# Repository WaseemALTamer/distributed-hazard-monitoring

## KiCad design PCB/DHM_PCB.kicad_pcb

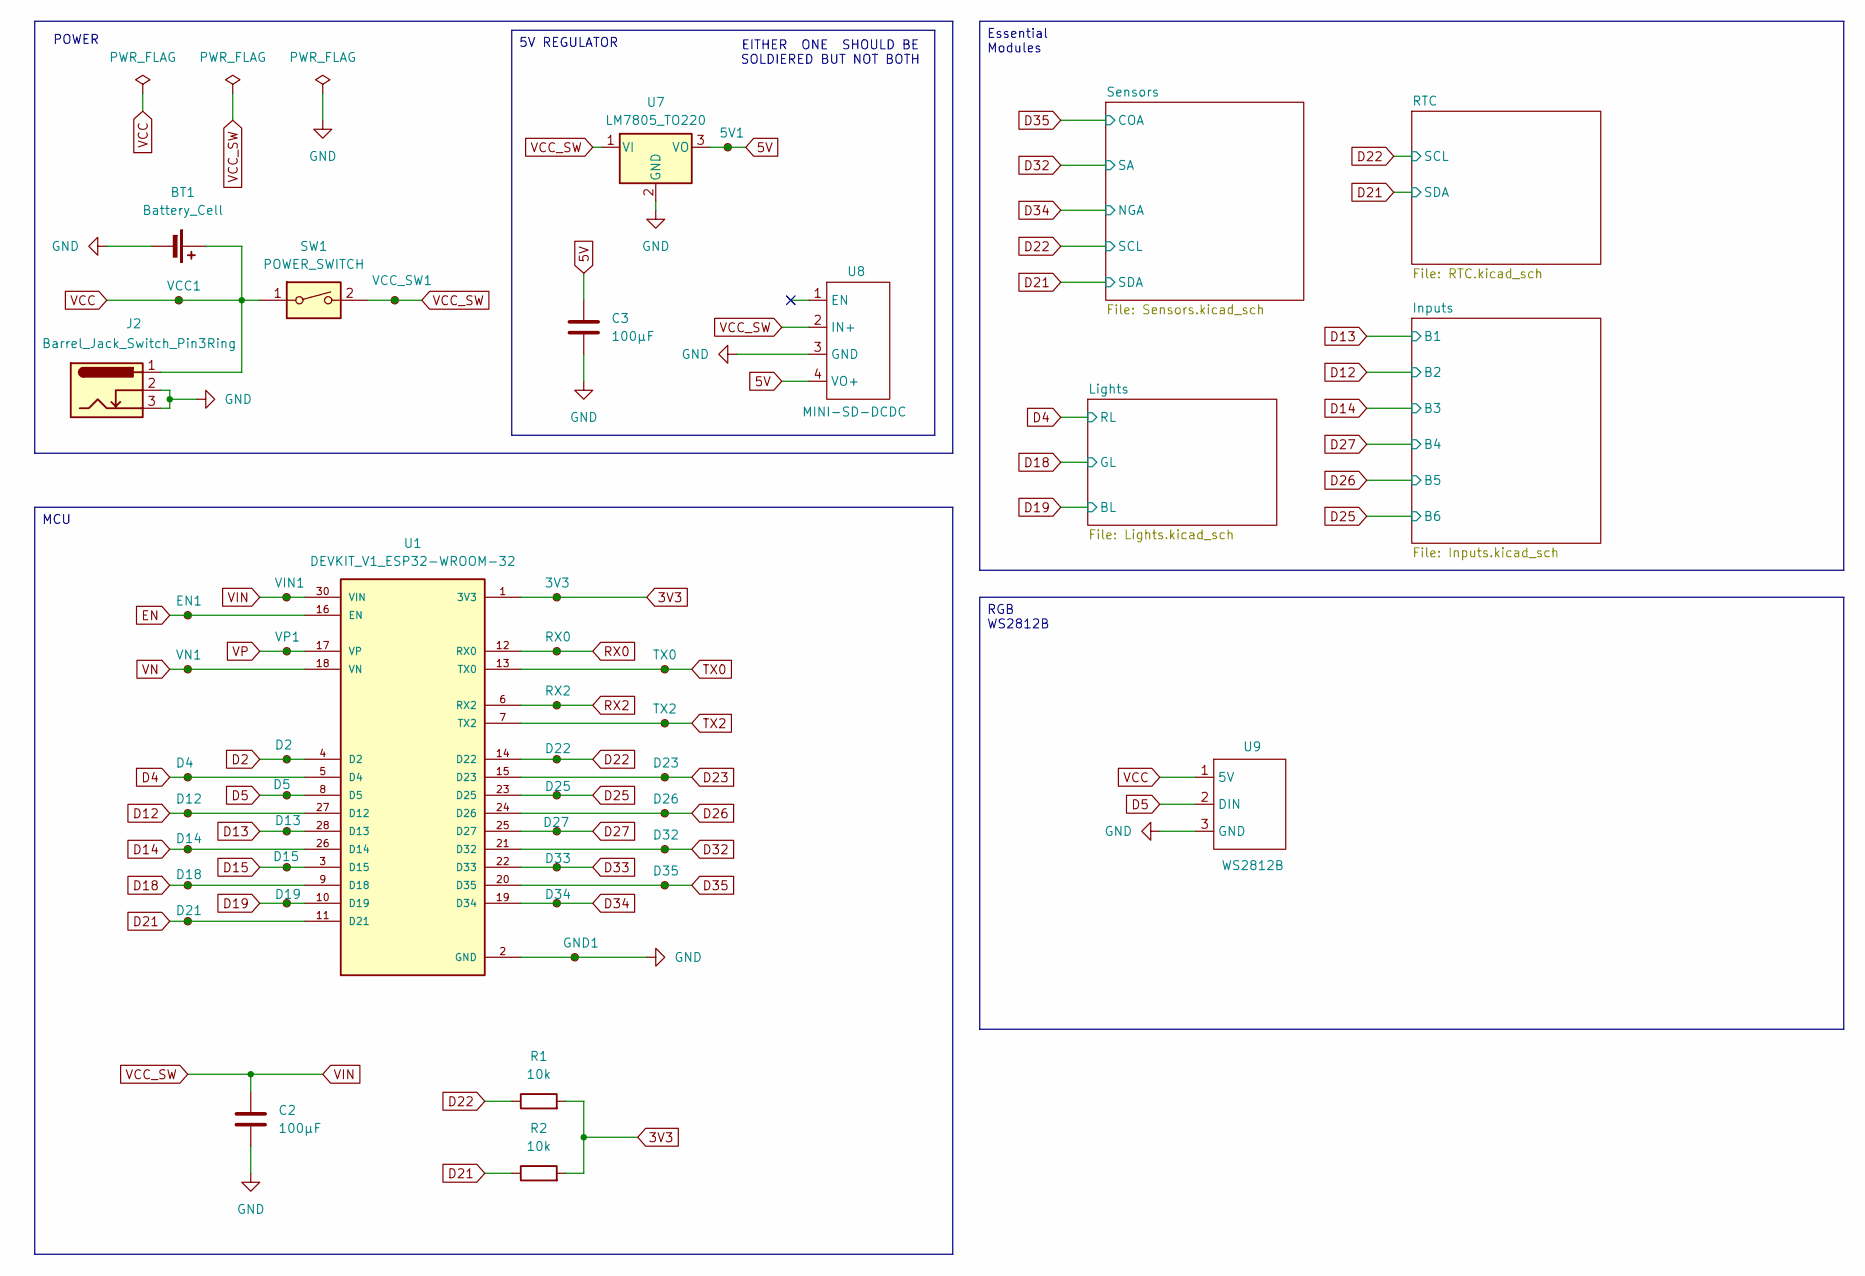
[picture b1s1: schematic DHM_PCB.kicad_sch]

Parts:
3V3, 5V1: TestPoint_Small; PinHeader_1x04_P2.54mm_Vertical_Custum_shortedpins
BT1: Battery_Cell; BatteryHolder_Eagle_12BH611-GR
C2, C3: 100µF; CP_Radial_D5.0mm_P2.00mm
D2, D4, D5, D12, D13, D14, D15, D18, D19, D21, D22, D23, D25, D26, D27, D32, D33, D34, D35: TestPoint_Small; PinHeader_1x04_P2.54mm_Vertical_Custum_shortedpins
EN1: TestPoint_Small; PinHeader_1x04_P2.54mm_Vertical_Custum_shortedpins
GND1: TestPoint_Small; PinHeader_1x04_P2.54mm_Vertical_Custum_shortedpins
J2: Barrel_Jack_Switch_Pin3Ring; BarrelJack_GCT_DCJ200-10-A_Horizontal
R1, R2: 10k; R_Axial_DIN0207_L6.3mm_D2.5mm_P10.16mm_Horizontal
RX0, RX2: TestPoint_Small; PinHeader_1x04_P2.54mm_Vertical_Custum_shortedpins
SW1: POWER_SWITCH; PinHeader_1x02_P2.54mm_Vertical
TX0, TX2: TestPoint_Small; PinHeader_1x04_P2.54mm_Vertical_Custum_shortedpins
U1: DEVKIT_V1_ESP32-WROOM-32; MODULE_DEVKIT_V1_ESP32-WROOM-32; MPN DEVKIT V1 ESP32-WROOM-32
U7: LM7805_TO220; TO-220-3_Vertical
U8: MINI-SD-DCDC; PinHeader_1x04_P2.54mm_Vertical
U9: WS2812B; TerminalBlock_Phoenix_MPT-0,5-3-2.54_1x03_P2.54mm_Horizontal
VCC1: TestPoint_Small; PinHeader_1x04_P2.54mm_Vertical_Custum_shortedpins
VCC_SW1: TestPoint_Small; PinHeader_1x04_P2.54mm_Vertical_Custum_shortedpins
VIN1: TestPoint_Small; PinHeader_1x04_P2.54mm_Vertical_Custum_shortedpins
VN1: TestPoint_Small; PinHeader_1x04_P2.54mm_Vertical_Custum_shortedpins
VP1: TestPoint_Small; PinHeader_1x04_P2.54mm_Vertical_Custum_shortedpins

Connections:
3V3: 3V3.1 (1_1), R1.2, R2.2, U1.1 (3V3); also elsewhere on the board
5V: 5V1.1 (1_1), C3.1, U7.3 (VO), U8.4 (VO+); also elsewhere on the board
D2: D2.1 (1_1), U1.4 (D2)
D4: D4.1 (1_1), U1.5 (D4); also elsewhere on the board
D5: D5.1 (1_1), U1.8 (D5), U9.2 (DIN)
D12: D12.1 (1_1), U1.27 (D12); also elsewhere on the board
D13: D13.1 (1_1), U1.28 (D13); also elsewhere on the board
D14: D14.1 (1_1), U1.26 (D14); also elsewhere on the board
D15: D15.1 (1_1), U1.3 (D15)
D18: D18.1 (1_1), U1.9 (D18); also elsewhere on the board
D19: D19.1 (1_1), U1.10 (D19); also elsewhere on the board
D21: D21.1 (1_1), R2.1, U1.11 (D21); also elsewhere on the board
D22: D22.1 (1_1), R1.1, U1.14 (D22); also elsewhere on the board
D23: D23.1 (1_1), U1.15 (D23)
D25: D25.1 (1_1), U1.23 (D25); also elsewhere on the board
D26: D26.1 (1_1), U1.24 (D26); also elsewhere on the board
D27: D27.1 (1_1), U1.25 (D27); also elsewhere on the board
D32: D32.1 (1_1), U1.21 (D32); also elsewhere on the board
D33: D33.1 (1_1), U1.22 (D33)
D34: D34.1 (1_1), U1.19 (D34); also elsewhere on the board
D35: D35.1 (1_1), U1.20 (D35); also elsewhere on the board
EN: EN1.1 (1_1), U1.16 (EN)
GND: BT1.2 (-), C2.2, C3.2, GND1.1 (1_1), J2.2, J2.3, U1.2 (GND), U1.29 (GND), U7.2 (GND), U8.3 (GND), U9.3 (GND); also elsewhere on the board
RX0: RX0.1 (1_1), U1.12 (RX0)
RX2: RX2.1 (1_1), U1.6 (RX2)
TX0: TX0.1 (1_1), U1.13 (TX0)
TX2: TX2.1 (1_1), U1.7 (TX2)
VCC: BT1.1 (+), J2.1, SW1.1, U9.1 (5V), VCC1.1 (1_1)
VCC_SW: C2.1, SW1.2, U1.30 (VIN), U7.1 (VI), U8.2 (IN+), VCC_SW1.1 (1_1), VIN1.1 (1_1)
VN: U1.18 (VN), VN1.1 (1_1)
VP: U1.17 (VP), VP1.1 (1_1)

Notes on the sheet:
EITHER ONE SHOULD BE SOLDIERED BUT NOT BOTH
POWER
Essential Modules
RGB WS2812B
5V REGULATOR
MCU

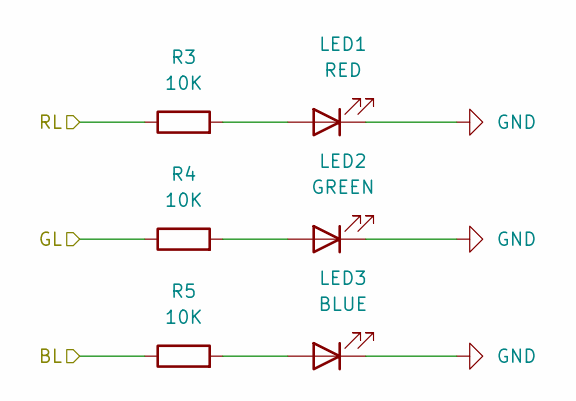
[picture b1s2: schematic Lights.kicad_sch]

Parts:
LED1: RED; LED_D5.0mm
LED2: GREEN; LED_D5.0mm
LED3: BLUE; LED_D5.0mm
R3, R4, R5: 10K; R_Axial_DIN0207_L6.3mm_D2.5mm_P10.16mm_Horizontal

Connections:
D4: R3.1; also elsewhere on the board
D18: R4.1; also elsewhere on the board
D19: R5.1; also elsewhere on the board
GND: LED1.1 (K), LED2.1 (K), LED3.1 (K); also elsewhere on the board
unnamed: LED1.2 (A), R3.2
unnamed: LED2.2 (A), R4.2
unnamed: LED3.2 (A), R5.2

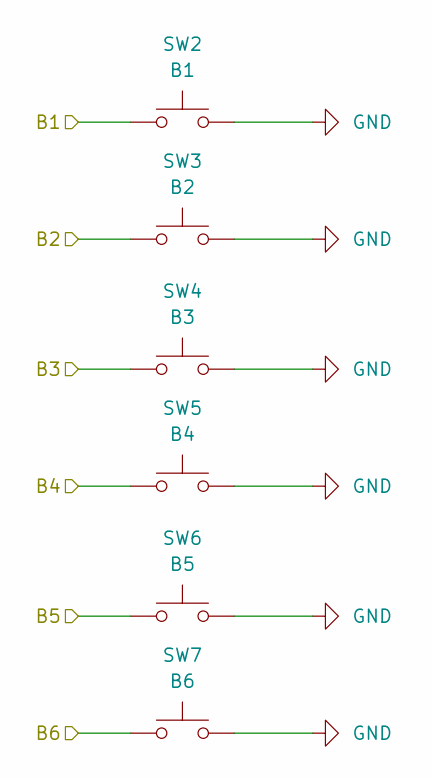
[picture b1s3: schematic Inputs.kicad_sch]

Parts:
SW2: B1; SW_PUSH_6mm_H4.3mm
SW3: B2; SW_PUSH_6mm_H4.3mm
SW4: B3; SW_PUSH_6mm_H4.3mm
SW5: B4; SW_PUSH_6mm_H4.3mm
SW6: B5; SW_PUSH_6mm_H4.3mm
SW7: B6; SW_PUSH_6mm_H4.3mm

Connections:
D12: SW3.1; also elsewhere on the board
D13: SW2.1; also elsewhere on the board
D14: SW4.1; also elsewhere on the board
D25: SW7.1; also elsewhere on the board
D26: SW6.1; also elsewhere on the board
D27: SW5.1; also elsewhere on the board
GND: SW2.2, SW3.2, SW4.2, SW5.2, SW6.2, SW7.2; also elsewhere on the board

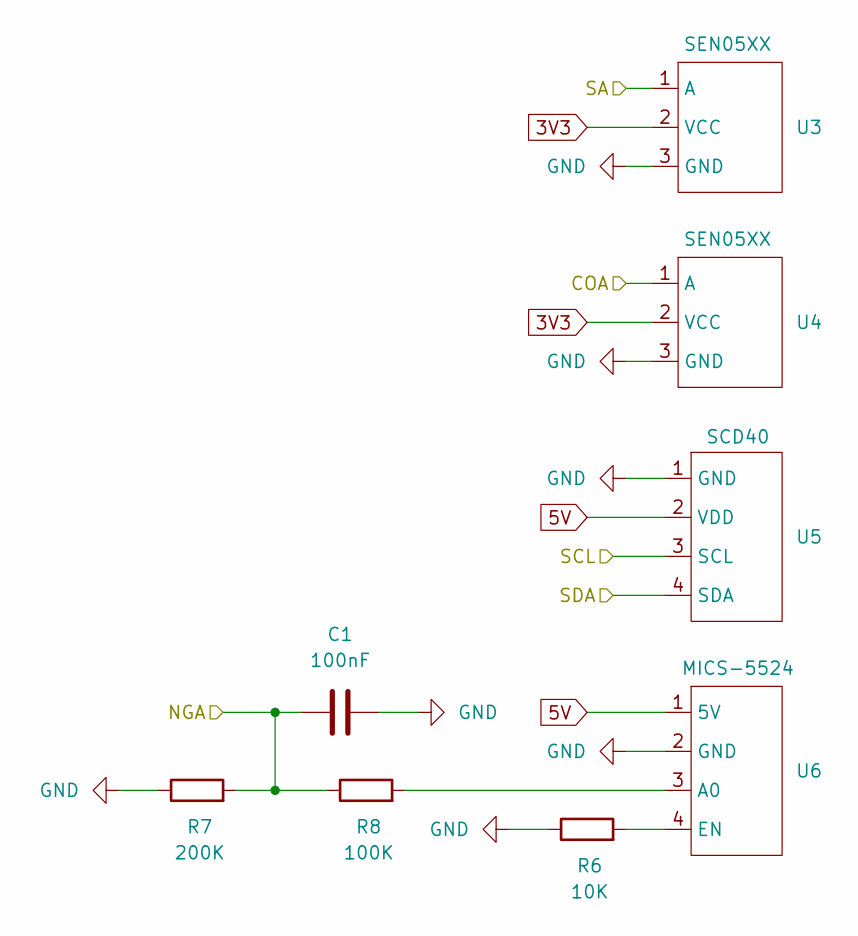
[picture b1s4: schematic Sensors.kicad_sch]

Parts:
C1: 100nF; C_Disc_D5.0mm_W2.5mm_P5.00mm
R6: 10K; R_Axial_DIN0207_L6.3mm_D2.5mm_P10.16mm_Horizontal
R7: 200K; R_Axial_DIN0207_L6.3mm_D2.5mm_P10.16mm_Horizontal
R8: 100K; R_Axial_DIN0207_L6.3mm_D2.5mm_P10.16mm_Horizontal
U3, U4: SEN05XX; PinHeader_1x03_P2.54mm_Vertical
U5: SCD40; PinHeader_1x04_P2.54mm_Vertical
U6: MICS-5524; PinHeader_1x04_P2.54mm_Vertical

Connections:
3V3: U3.2 (VCC), U4.2 (VCC); also elsewhere on the board
5V: U5.2 (VDD), U6.1 (5V); also elsewhere on the board
D21: U5.4 (SDA); also elsewhere on the board
D22: U5.3 (SCL); also elsewhere on the board
D32: U3.1 (A); also elsewhere on the board
D34: C1.1, R7.2, R8.1; also elsewhere on the board
D35: U4.1 (A); also elsewhere on the board
GND: C1.2, R6.1, R7.1, U3.3 (GND), U4.3 (GND), U5.1 (GND), U6.2 (GND); also elsewhere on the board
unnamed: R8.2, U6.3 (A0)
unnamed: R6.2, U6.4 (EN)

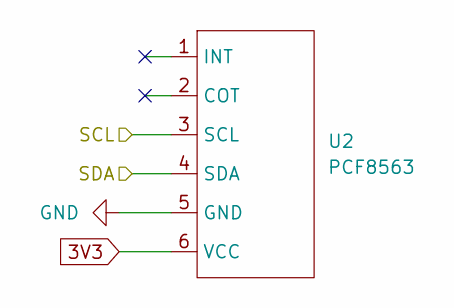
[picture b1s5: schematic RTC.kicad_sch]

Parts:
U2: PCF8563; PinHeader_1x06_P2.54mm_Vertical

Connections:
3V3: U2.6 (VCC); also elsewhere on the board
D21: U2.4 (SDA); also elsewhere on the board
D22: U2.3 (SCL); also elsewhere on the board
GND: U2.5 (GND); also elsewhere on the board

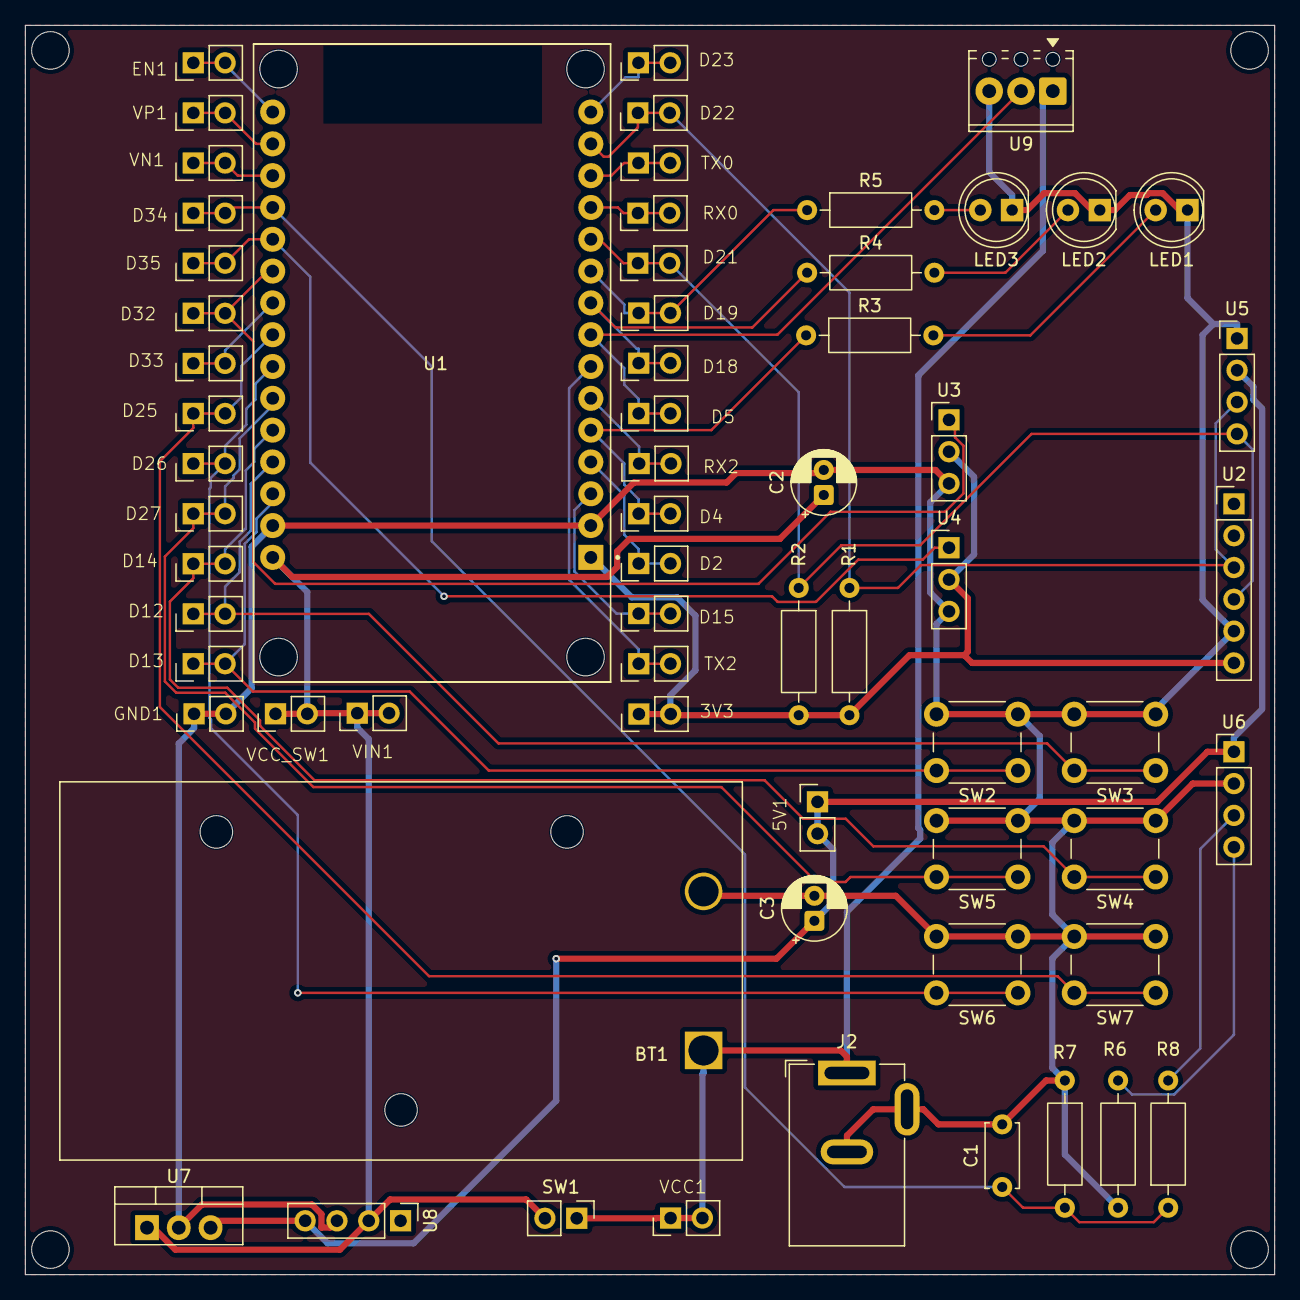
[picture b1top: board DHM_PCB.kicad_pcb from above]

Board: 2 copper layers, 99.8 x 99.8 mm, 64 parts (0 on the bottom side), 36 nets.
